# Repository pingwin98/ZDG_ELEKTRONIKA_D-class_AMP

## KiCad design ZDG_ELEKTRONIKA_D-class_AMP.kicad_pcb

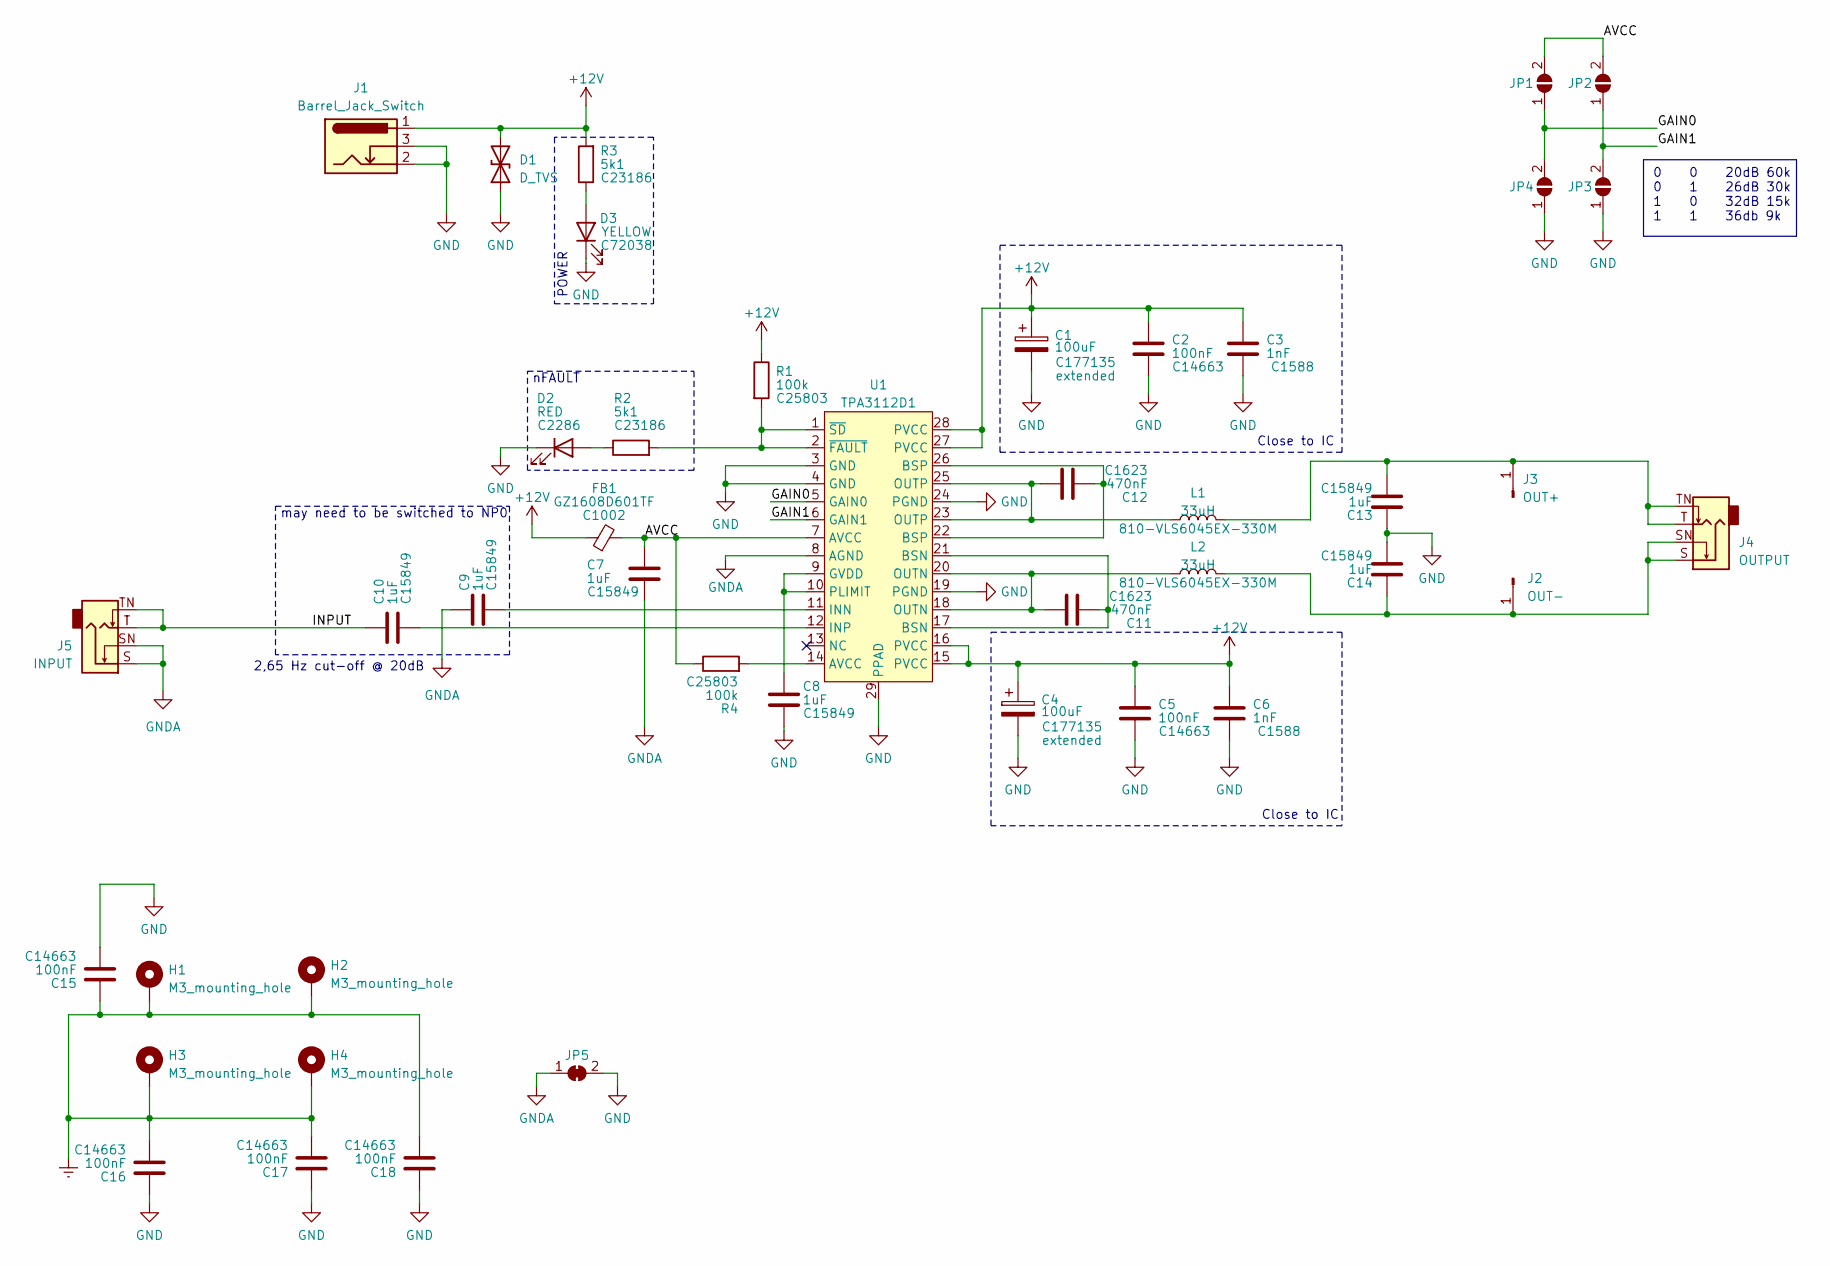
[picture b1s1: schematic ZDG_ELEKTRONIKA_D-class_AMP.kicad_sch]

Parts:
C1, C4: 100uF; CP_Elec_4x5.4; LCSC C177135
C2, C5, C15, C16, C17, C18: 100nF; C_0603_1608Metric_Pad1.08x0.95mm_HandSolder; LCSC C14663
C3, C6: 1nF; C_0603_1608Metric_Pad1.08x0.95mm_HandSolder; LCSC C1588
C7, C8, C9, C10, C13, C14: 1uF; C_0603_1608Metric_Pad1.08x0.95mm_HandSolder; LCSC C15849
C11, C12: 470nF; C_0603_1608Metric_Pad1.08x0.95mm_HandSolder; LCSC C1623
D1: D_TVS; D_SMA-SMB_Universal_Handsoldering
D2: RED; LED_0603_1608Metric_Pad1.05x0.95mm_HandSolder; LCSC C2286
D3: YELLOW; LED_0603_1608Metric_Pad1.05x0.95mm_HandSolder; LCSC C72038
FB1: GZ1608D601TF; L_0603_1608Metric_Pad1.05x0.95mm_HandSolder; LCSC C1002
H1, H2, H3, H4: M3_mounting_hole; MountingHole_3.2mm_M3_DIN965_Pad
J1: Barrel_Jack_Switch; BarrelJack_GCT_DCJ200-10-A_Horizontal
J2: OUT-; Pin_D1.0mm_L10.0mm
J3: OUT+; Pin_D1.0mm_L10.0mm
J4: OUTPUT; Jack_6.35mm_Neutrik_NMJ4HCD2_Horizontal
J5: INPUT; Jack_6.35mm_Neutrik_NMJ4HCD2_Horizontal
JP1, JP2, JP3, JP4: SolderJumper_2_Open; SolderJumper-2_P1.3mm_Open_Pad1.0x1.5mm
JP5: SolderJumper_2_Bridged; SolderJumper-2_P1.3mm_Bridged2Bar_Pad1.0x1.5mm
L1, L2: 33uH; L_TDK_VLS6045EX_VLS6045AF; Mouser 810-VLS6045EX-330M
R1, R4: 100k; R_0603_1608Metric_Pad0.98x0.95mm_HandSolder; LCSC C25803
R2, R3: 5k1; R_0603_1608Metric_Pad0.98x0.95mm_HandSolder; LCSC C23186
U1: TPA3112D1; HTSSOP-28-1EP_4.4x9.7mm_P0.65mm_EP2.85x5.4mm

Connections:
+12V: C1.1, C2.1, C3.1, C4.1, C5.1, C6.1, D1.2 (A2), FB1.1, J1.1, R1.1, R3.2, U1.15 (PVCC), U1.16 (PVCC), U1.27 (PVCC), U1.28 (PVCC)
/AVCC: C7.1, FB1.2, JP1.2 (B), JP2.2 (B), R4.1, U1.7 (AVCC)
/GAIN0: JP1.1 (A), JP4.2 (B), U1.5 (GAIN0)
/GAIN1: JP2.1 (A), JP3.2 (B), U1.6 (GAIN1)
/INPUT: C10.1, J5.T, J5.TN
Earth: C15.1, C16.2, C17.2, C18.2, H1.1, H2.1, H3.1, H4.1
GND: C1.2, C2.2, C3.2, C4.2, C5.2, C6.2, C8.2, C13.1, C14.2, C15.2, C16.1, C17.1, C18.1, D1.1 (A1), D2.1 (K), D3.1 (K), J1.2, J1.3, JP3.1 (A), JP4.1 (A), JP5.2 (B), U1.3 (GND), U1.4 (GND), U1.19 (PGND), U1.24 (PGND), U1.29 (PPAD)
GNDA: C7.2, C9.1, J5.S, J5.SN, JP5.1 (A), U1.8 (AGND)
unnamed: C11.1, L2.1, U1.18 (OUTN), U1.20 (OUTN)
unnamed: C11.2, U1.17 (BSN), U1.21 (BSN)
unnamed: C12.1, L1.1, U1.23 (OUTP), U1.25 (OUTP)
unnamed: C12.2, U1.22 (BSP), U1.26 (BSP)
unnamed: D2.2 (A), R2.1
unnamed: D3.2 (A), R3.1
unnamed: C14.1, J2.1, J4.S, J4.SN, L2.2
unnamed: C13.2, J3.1, J4.T, J4.TN, L1.2
unnamed: R4.2, U1.14 (AVCC)
unnamed: C8.1, U1.9 (GVDD), U1.10 (PLIMIT)
unnamed: C9.2, U1.11 (INN)
unnamed: C10.2, U1.12 (INP)
unnamed: R1.2, R2.2, U1.1 (~SD), U1.2 (~FAULT)

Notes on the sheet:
2,65 Hz cut-off @ 20dB
POWER
0 0 20dB 60k 0 1 26dB 30k 1 0 32dB 15k 1 1 36db 9k
Close to IC
may need to be switched to NP0
nFAULT

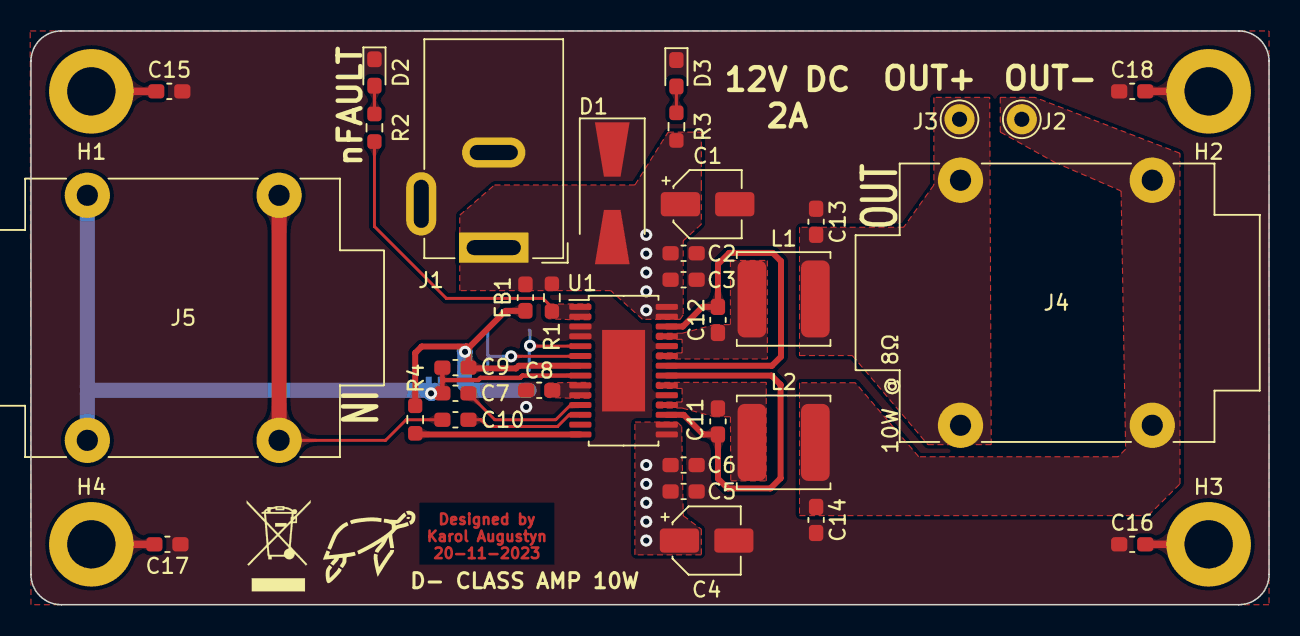
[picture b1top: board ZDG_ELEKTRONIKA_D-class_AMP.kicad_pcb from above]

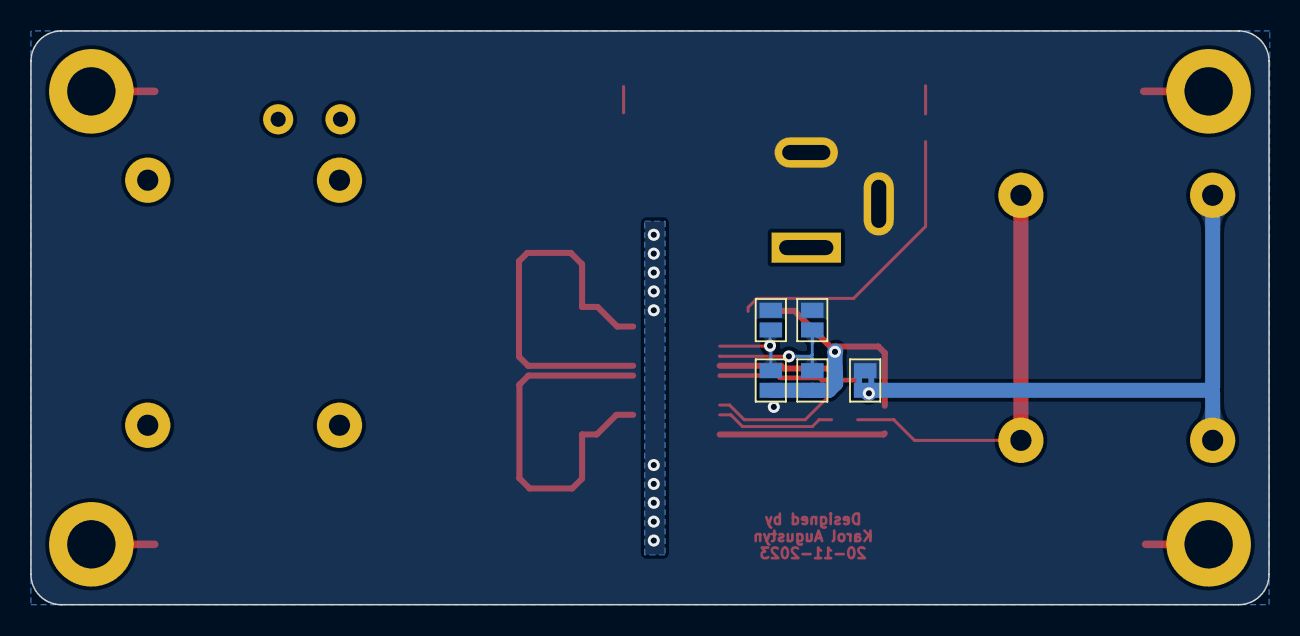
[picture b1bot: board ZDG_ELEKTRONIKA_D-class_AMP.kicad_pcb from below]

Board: 2 copper layers, 82.0 x 38.0 mm, 43 parts (5 on the bottom side), 21 nets.

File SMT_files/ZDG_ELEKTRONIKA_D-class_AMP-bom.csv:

"Comment","Designator","Footprint","LCSC"
"100uF","C1, C4","Capacitor_SMD:CP_Elec_4x5.4","C177135"
"100nF","C2, C5, C15, C16, C17, C18","Capacitor_SMD:C_0603_1608Metric_Pad1.08x0.95mm_HandSolder","C14663"
"1nF","C3, C6","Capacitor_SMD:C_0603_1608Metric_Pad1.08x0.95mm_HandSolder","C1588"
"1uF","C7, C8, C9, C10, C13, C14","Capacitor_SMD:C_0603_1608Metric_Pad1.08x0.95mm_HandSolder","C15849"
"470nF","C11, C12","Capacitor_SMD:C_0603_1608Metric_Pad1.08x0.95mm_HandSolder","C1623"
"D_TVS","D1","Diode_SMD:D_SMA-SMB_Universal_Handsoldering",""
"RED","D2","LED_SMD:LED_0603_1608Metric_Pad1.05x0.95mm_HandSolder","C2286"
"YELLOW","D3","LED_SMD:LED_0603_1608Metric_Pad1.05x0.95mm_HandSolder","C72038"
"GZ1608D601TF","FB1","Inductor_SMD:L_0603_1608Metric_Pad1.05x0.95mm_HandSolder","C1002"
"Barrel_Jack_Switch","J1","Connector_BarrelJack:BarrelJack_GCT_DCJ200-10-A_Horizontal",""
"OUT-","J2","Connector_Pin:Pin_D1.0mm_L10.0mm",""
"OUT+","J3","Connector_Pin:Pin_D1.0mm_L10.0mm",""
"OUTPUT","J4","Connector_Audio:Jack_6.35mm_Neutrik_NMJ4HCD2_Horizontal",""
"INPUT","J5","Connector_Audio:Jack_6.35mm_Neutrik_NMJ4HCD2_Horizontal",""
"SolderJumper_2_Open","JP1, JP2, JP3, JP4","Jumper:SolderJumper-2_P1.3mm_Open_Pad1.0x1.5mm",""
"SolderJumper_2_Bridged","JP5","Jumper:SolderJumper-2_P1.3mm_Bridged2Bar_Pad1.0x1.5mm",""
"33uH","L1, L2","Inductor_SMD:L_TDK_VLS6045EX_VLS6045AF",""
"100k","R1, R4","Resistor_SMD:R_0603_1608Metric_Pad0.98x0.95mm_HandSolder","C25803"
"5k1","R2, R3","Resistor_SMD:R_0603_1608Metric_Pad0.98x0.95mm_HandSolder","C23186"
"TPA3112D1","U1","Package_SO:HTSSOP-28-1EP_4.4x9.7mm_P0.65mm_EP2.85x5.4mm",""

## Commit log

2023-11-20 finito
2023-11-21 production files prepared
2023-12-07 html bom
